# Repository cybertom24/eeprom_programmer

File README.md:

# eeprom_programmer
A repository to build a programmer for eeprom based ion arduino nano

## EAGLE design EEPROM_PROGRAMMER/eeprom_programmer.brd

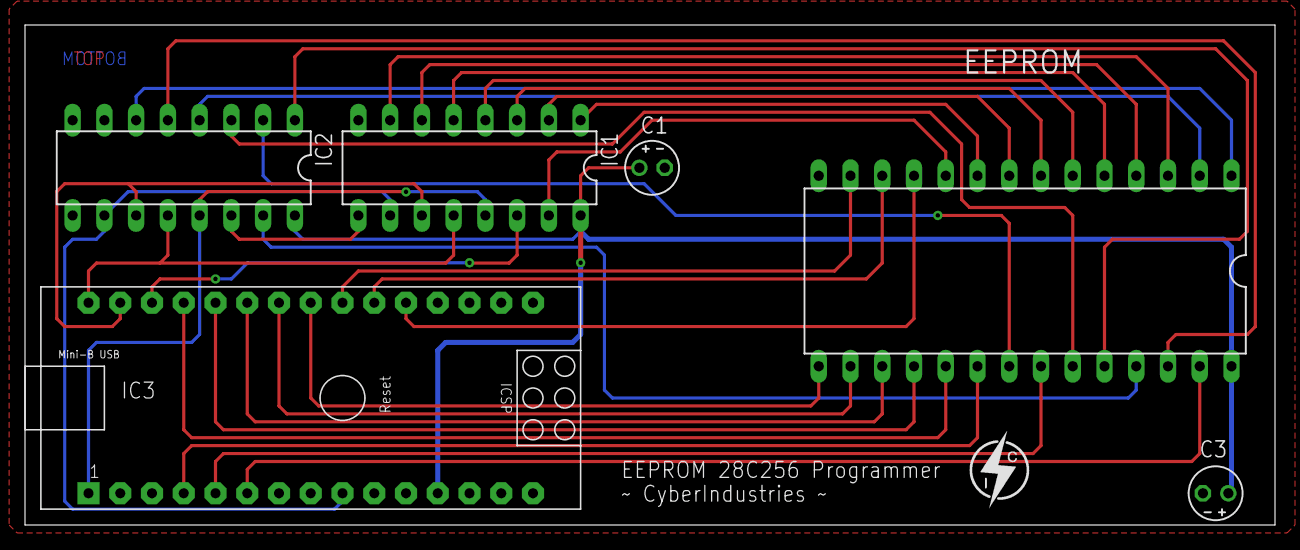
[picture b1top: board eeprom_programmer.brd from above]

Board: 2 copper layers, 100.0 x 40.0 mm, 7 parts (0 on the bottom side), 34 nets.

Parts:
C1, C3: 1uF; E2-4
EEPROM: AT28C256-28DIP; DIL28-6
IC1, IC2: 74HC595N; DIL16
IC3: ARDUINO_NANO
U$1: LOGO-CYBERINDUSTRIES"; LOGO-SMALL

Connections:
A0: EEPROM.10, IC1.15
A1: EEPROM.9, IC1.1
A2: EEPROM.8, IC1.2
A3: EEPROM.7, IC1.3
A4: EEPROM.6, IC1.4
A5: EEPROM.5, IC1.5
A6: EEPROM.4, IC1.6
A7: EEPROM.3, IC1.7
A8: EEPROM.25, IC2.15
A9: EEPROM.24, IC2.1
A10: EEPROM.21, IC2.2
A11: EEPROM.23, IC2.3
A12: EEPROM.2, IC2.4
A13: EEPROM.26, IC2.5
A14: EEPROM.1, IC2.6
CE: EEPROM.20, IC3.4
G: IC1.13, IC2.13, IC3.1
GND: C1.-, C3.-, EEPROM.14, IC1.8, IC2.8, IC3.14, IC3.19
IO0: EEPROM.11, IC3.20
IO1: EEPROM.12, IC3.21
IO2: EEPROM.13, IC3.22
IO3: EEPROM.15, IC3.23
IO4: EEPROM.16, IC3.24
IO5: EEPROM.17, IC3.25
IO6: EEPROM.18, IC3.26
IO7: EEPROM.19, IC3.27
unnamed: IC1.9, IC2.14
OE: EEPROM.22, IC3.5
RCK: IC1.12, IC2.12, IC3.30
SCK: IC1.11, IC2.11, IC3.29
SCL: IC1.10, IC2.10, IC3.9
SER: IC1.14, IC3.28
VCC: C1.+, C3.+, EEPROM.28, IC1.16, IC2.16, IC3.12
WE: EEPROM.27, IC3.6

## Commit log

2022-07-03 commit iniziale
2022-07-03 secondo commit
2022-07-03 initiate repo
2022-07-03 simplified code
2022-07-03 minor changes
2022-07-03 expanded eepromManager: removed modes and created mainMenu(9
2022-07-05 added page writing
2022-07-08 added validation
2022-07-22 roba varia
2022-08-23 ci ho provato...
2022-09-09 tried to fix issues, nothing worked
2023-04-05 sistemato pcb
2023-07-19 Aggiornata un po' di roba
2024-02-10 roba
